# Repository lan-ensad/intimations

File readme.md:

# Intimations of Shanshui

<!-- TOC -->
- [Interactive Sculpture](#interactive-sculpture)
  - [Interaction & Space Mapping Logic](#interaction--space-mapping-logic)
  - [network diagram](#network-diagram)
  - [mechanics](#mechanics)
  - [electronics](#electronics)
- [Installation](#installation)
  - [Raspberry](#raspberry)
    - [DAC+](#dac)
    - [NodeRed](#nodered)
    - [Pure Data](#pure-data)
    - [Mosquitto](#mosquitto)
<!-- /TOC -->

## Interactive Sculpture

|||
|--|--|
|Artists/Creators|Vivian Wang, Martin De Bie, Olivier Bienz|
|Title, Year|Intimations of Shanshui, 2024|
|Exhibition Location|Shanshui: Echoes & Signals, M+ Hong Kong|
|Media|Interactive textile sculpture with sound, light, movement, and sensors|
|Logic/Description|For Intimations, we created a structural concept around the idea of circular layers. This sculpture crafted from fabric creates a focused and immersive experience blending sound, movement, and light. Variations in sound, light and movement respond to human presence and circumnavigation, unfolding in a slow and deliberate choreography of the different elements. The work is an ode to Shanshui painting, bridging tradition and modernity through an interactive exchange and the composition of textile and sound, with special detail given to how lighting dramatically alters the visual impact of the mountains.|
|||

### Interaction & Space Mapping Logic

There are 6 distance sensors on the sculpture. They are labelled S_00 to S_05. S_02 and S_05 are at the entry and exit points of the display location called the Breakout Room. To trigger sound and light activity, we partitioned the interaction zones into 6 zones labelled A, B, C, D, E and F.

**Sounds** are activated by presence within zones. All zones have an inner and an outer zone and these measurements are not the same for each zone. The rationale is to have something a little more organic in shape. For example, Zone D has an inner zone that goes up to 500mm, and its outer zone extends up to 2000mm whereas Zone F has an inner zone of 400mm and the outer extends only up to 1100mm. Anything outside of 1100mm will register a value on the sensor but it will not trigger a sound. We also programmed sounds to trigger when 2 zones register a value at the same time, meaning the sensors in these zones have to sense two separate persons in order to activate a sound. Certain sounds will also only trigger after a delay value of say 29656ms in the outer zone of Zone D. This gives some nuance and variation to the sounds and does not create cacophony for every interaction that happens each time a sensor value is registered. These 2-zone combinations are also varied between inner and outer zones. For each specific zone within zones A-F, there are also sometimes 2 or 3 files that are randomised to create more diverse combinations of sounds.

**Light** colour combinations are also varied. Each concentric circle has between 3-5 sectors of LEDs that light up. The colour sectors are irregular, so as to create organic combinations of light and shadow play between the layers of textile. Different behaviours are triggered depending of how many zones are active during a certain amount of time. Each colour sequence is scripted to create a sense of rhythm and movement and the colours are selected according to a predefined colour palette.

**Movement** of the 4 circular rings/layers of textile mountains are programmed and follow its own logic. Between 90000ms to 120000ms, different combinations of rings 1,2,3 will move. The duration of movement varies between 3000ms and 20000ms. The direction of the oscillation is randomised. The rings could move in the same direction or in opposite directions. Once a day, all 4 rings move.

### network diagram

### mechanics

Principles assembly

You can find all details and print parts in the *3d/* folder.

### electronics

**All firmeware available in *firmeware/< shield >* folder**\
**All schematics and gerber available in *pcb/mhk* folder in KiCad project format**

components :
- Global:
  - Raspberry Pi
  - [DAC+](https://www.raspberrypi.com/products/dac-plus/)
  - [router](https://www.gl-inet.com/products/gl-b1300/), setup for zeroTier vpn support
  - [PowerSupply +5V](https://www.meanwell.fr/ac-dc-ultra-slim-din-rail-power-supply-input-range-hdr--30--5), for the Raspberry Pi and the shields
  - [PowerSupply +12V](https://www.meanwell.fr/ac-dc-ultra-slim-din-rail-power-supply-input-range-hdr--30--12), for the router

- Motors Shield:
  - [dagu WT751](https://www.gotronic.fr/art-motoreducteur-wt751-17751.htm), motor 6Vcc
  - [drv8838](https://www.pololu.com/product/2990), driver motor, 0→11V
  - [optical endstop](https://www.amazon.fr/GeeekPi-Optical-Endstop-Photoelectric-imprimante/dp/B086P7XHJ2/ref=sr_1_7?__mk_fr_FR=%C3%85M%C3%85%C5%BD%C3%95%C3%91&crid=303ZPGFLA8E0W&keywords=optical+switch&qid=1706533943&sprefix=optical+switch%2Caps%2C99&sr=8-7)
  - [Raspberry Pico Wifi](https://www.raspberrypi.com/products/raspberry-pi-pico/), micropython

- Leds Shield:
  - WS2812 led strip, 5V
  - [Raspberry Pico Wifi](https://www.raspberrypi.com/products/raspberry-pi-pico/), micropython

- Sensors Shield:
  - [HC-SR04](https://www.gotronic.fr/art-module-de-detection-us-hc-sr04-20912.htm), ultrasonic sensors
  - [Raspberry Pico Wifi](https://www.raspberrypi.com/products/raspberry-pi-pico/), micropython

**All details available in *pcb/mhk* KiCad project**

## Installation

### Raspberry

#### DAC+

[dac+](https://www.raspberrypi.com/products/dac-plus/)

* Install \
  Plug the shield on the RaspberryPi

`sudo nano /boot/config.txt --line`

l.6. > comment `#dtparam=i2c_arm=on`\
l.7. > enable `dtparam=i2s=on`\
l.8. > comment `#dtparam=spi=on`\
l.11 > comment `#dtparam=audio=on`\
l.12 > enable `dtoverlay=iqaudio-dac`\
l.27 > verify `dtoverlay=vc4-kms-v3d,noaudi` > (cut hdmi audio)

**All config files are in *dacplus/config.txt* folder**

#### NodeRed

* Install \
  [NodeRed](https://nodered.org/docs/getting-started/raspberrypi)
* Install dashboard \
  Palette > Install > *node-red-dashboard*

**The flow is available in the *nodered/flows.json* folder.**

#### Pure Data

* Install

```
sudo apt update && sudo apt upgrade -y

sudo apt install puredata -y
```

**The patch is available in the *puredata/_expo_patch.pd* folder.**

#### Mosquitto

* Install

```
sudo apt update && sudo apt upgrade -y

sudo apt install mosquitto mosquitto-clients -y

sudo systemctl enable mosquitto.service
```

* Edit config \
  `sudo nano /etc/mosquitto/mosquitto.conf`

add in the end :

```
listener 1883
allow_anonymous true
```

**Check the installation :**
* subscribe command line \
  `mosquitto_sub -d -t <topic>` (anonymous)\
  `mosquitto_sub -d -t <topic> -u <user> -P <pass>` (logged)
* publish command line \
  `mosquitto_pub -d -t <topic> -m "<Message>"` (anonymous)\
  `mosquitto_pub -d -t <topic> -m "<Message>" -u <user> -P <pass>` (logged)

  #### WIFI

`sudo nano /etc/wpa_spplicant/wpa_supplicant.conf`

```
network{
  scan_ssid=1
  ssid="<SSID>"
  psk="<PASSWORD>"
  key_mgmt=WPA-PSK
}
```

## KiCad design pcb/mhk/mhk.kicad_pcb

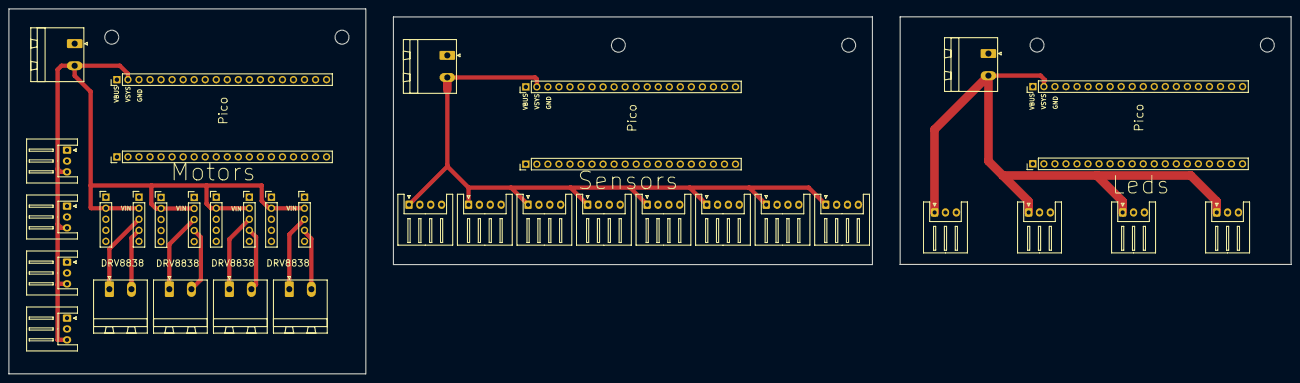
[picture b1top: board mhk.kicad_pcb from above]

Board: 4 copper layers, 295.1 x 84.0 mm, 43 parts (0 on the bottom side), 43 nets.

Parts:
H1, H1#2, H1#3, H2, H2#2, H2#3: MountingHole; MountingHole_3.2mm_M3
J1, J5, J6, J7, J8, J9, J10, J11: Conn_01x04_Socket; JST_XH_S4B-XH-A_1x04_P2.50mm_Horizontal
J2, J3, J12, J13, J21, J26: Conn_01x20_Socket; PinHeader_1x20_P2.54mm_Vertical
J4, J14, J20, J22, J23, J24, J25: Conn_01x02_Socket; PhoenixContact_MSTBA_2,5_2-G-5,08_1x02_P5.08mm_Horizontal
J15, J16, J17, J18, J31, J32, J33, J34: Conn_01x03_Socket; JST_XH_S3B-XH-A_1x03_P2.50mm_Horizontal
J27, J28, J29, J30, J35, J36, J37, J38: Conn_01x05_Socket; PinHeader_1x05_P2.54mm_Vertical

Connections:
+3.3V: J2.9, J13.5, J26.5
+5V: J1.1, J3.1, J3.2, J4.2, J5.1, J6.1, J7.1, J8.1, J9.1, J10.1, J11.1, J13.1, J13.2, J14.2, J15.1, J16.1, J17.1, J18.1, J20.2, J26.1, J26.2, J27.2, J28.2, J29.2, J30.2, J31.3, J32.3, J33.3, J34.3, J35.2, J36.2, J37.2, J38.2
DIN1: J12.5, J15.2
DIN2: J12.10, J16.2
DIN3: J12.15, J17.2
DIN4: J12.20, J18.2
ECHO1: J1.2, J2.1
ECHO2: J2.4, J5.2
ECHO3: J2.6, J6.2
ECHO4: J2.10, J7.2
ECHO5: J2.14, J8.2
ECHO6: J2.16, J9.2
ECHO7: J2.19, J10.2
ECHO8: J3.19, J11.2
EndStop1: J26.14, J31.2
EndStop2: J26.15, J32.2
EndStop3: J26.16, J33.2
EndStop4: J26.17, J34.2
GND: J1.4, J2.3, J2.8, J2.13, J2.18, J3.3, J3.8, J3.13, J3.18, J4.1, J5.4, J6.4, J7.4, J8.4, J9.4, J10.4, J11.4, J12.3, J12.8, J12.13, J12.18, J13.3, J13.8, J13.13, J13.18, J14.1, J15.3, J16.3, J17.3, J18.3, J20.1, J21.3, J21.8, J21.13, J21.18, J26.3, J26.8, J26.13, J26.18, J27.1, J28.1, J29.1, J30.1, J31.1, J32.1, J33.1, J34.1, J35.1, J36.1, J37.1, J38.1
MOTA1: J22.1, J29.3
MOTA2: J22.2, J29.4
MOTB1: J23.1, J30.3
MOTB2: J23.2, J30.4
MOTC1: J24.1, J37.3
MOTC2: J24.2, J37.4
MOTD1: J25.1, J38.3
MOTD2: J25.2, J38.4
PH1: J21.2, J27.4
PH2: J21.5, J28.4
PH3: J21.7, J35.4
PH4: J21.10, J36.4
PWM1: J21.1, J27.3
PWM2: J21.4, J28.3
PWM3: J21.6, J35.3
PWM4: J21.9, J36.3
TRIGGER1: J1.3, J2.2
TRIGGER2: J2.5, J5.3
TRIGGER3: J2.7, J6.3
TRIGGER4: J2.11, J7.3
TRIGGER5: J2.15, J8.3
TRIGGER6: J2.17, J9.3
TRIGGER7: J2.20, J10.3
TRIGGER8: J3.20, J11.3

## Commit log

2024-01-29 first push
2024-02-10 Create LICENSE
2024-04-05 Update main.py
    change snapshots timing for sensors
